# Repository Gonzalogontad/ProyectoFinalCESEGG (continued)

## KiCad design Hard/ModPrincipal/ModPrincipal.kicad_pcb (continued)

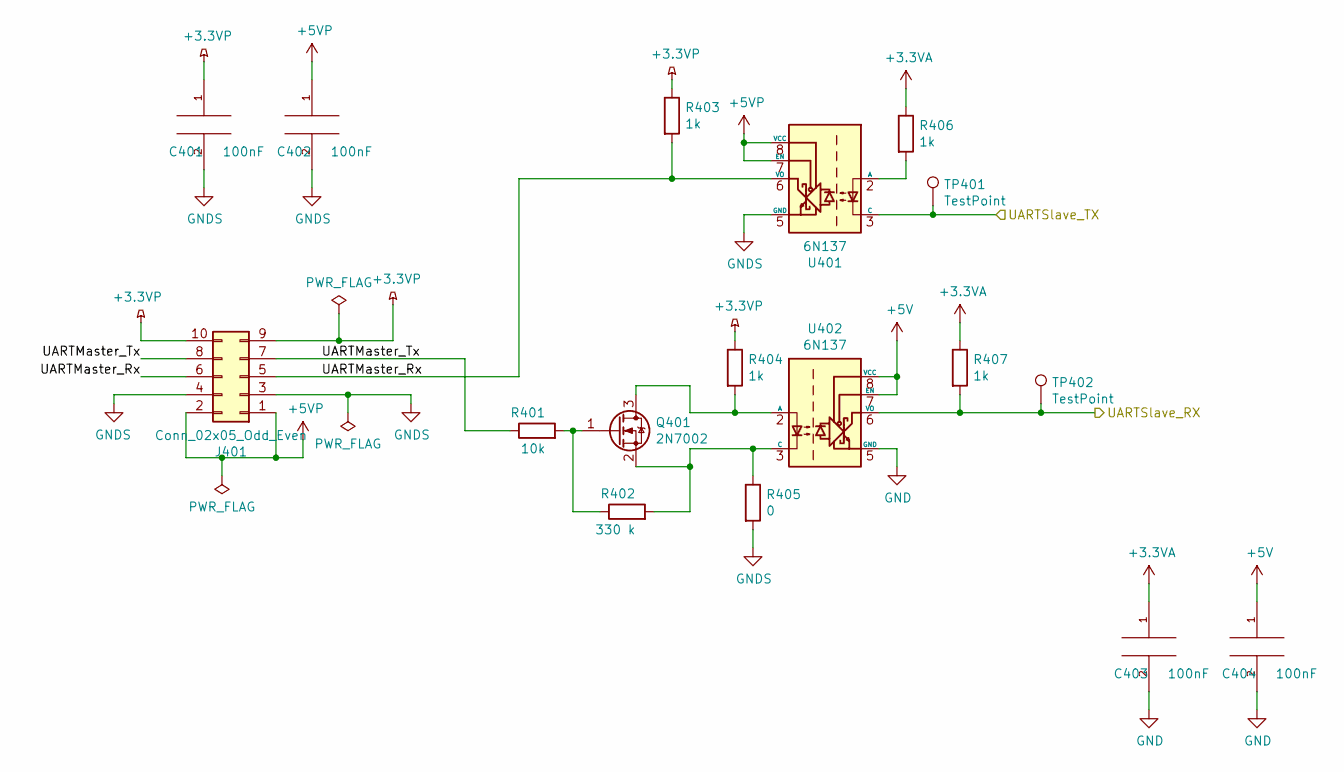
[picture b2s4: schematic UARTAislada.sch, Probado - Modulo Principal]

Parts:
C401, C402, C403, C404: 100nF; C_0805_2012Metric_Pad1.15x1.40mm_HandSolder
J401: Conn_02x05_Odd_Even; PinHeader_2x05_P2.54mm_Vertical
Q401: 2N7002; SOT-23
R401: 10k; R_0805_2012Metric_Pad1.15x1.40mm_HandSolder
R402: 330 k; R_0805_2012Metric_Pad1.15x1.40mm_HandSolder
R403, R404, R406, R407: 1k; R_0805_2012Metric_Pad1.15x1.40mm_HandSolder
R405: 0; R_0805_2012Metric_Pad1.15x1.40mm_HandSolder
TP401, TP402: TestPoint; TestPoint_Pad_D1.5mm
U401, U402: 6N137; DIP-8_W7.62mm

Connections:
+3.3VA: C403.1, R406.1, R407.1; also elsewhere on the board
+3.3VP: C401.1, J401.9, J401.10, R403.1, R404.1
+5V: C404.1, U402.7 (EN), U402.8 (VCC); also elsewhere on the board
+5VP: C402.1, J401.1, J401.2, U401.7 (EN), U401.8 (VCC)
/UARTAislada/UARTMaster_Rx: J401.5, J401.6, R403.2, U401.6 (VO)
/UARTAislada/UARTMaster_Tx: J401.7, J401.8, R401.1
/UARTAislada/UARTSlave_RX: R407.2, TP402.1, U402.6 (VO); also elsewhere on the board
/UARTAislada/UARTSlave_TX: TP401.1, U401.3 (C); also elsewhere on the board
GND: C403.2, C404.2, U402.5 (GND); also elsewhere on the board
GNDS: C401.2, C402.2, J401.3, J401.4, R405.2, U401.5 (GND)
unnamed: Q401.1 (G), R401.2, R402.1
unnamed: Q401.2 (S), R402.2, R405.1, U402.3 (C)
unnamed: Q401.3 (D), R404.2, U402.2 (A)
unnamed: R406.2, U401.2 (A)

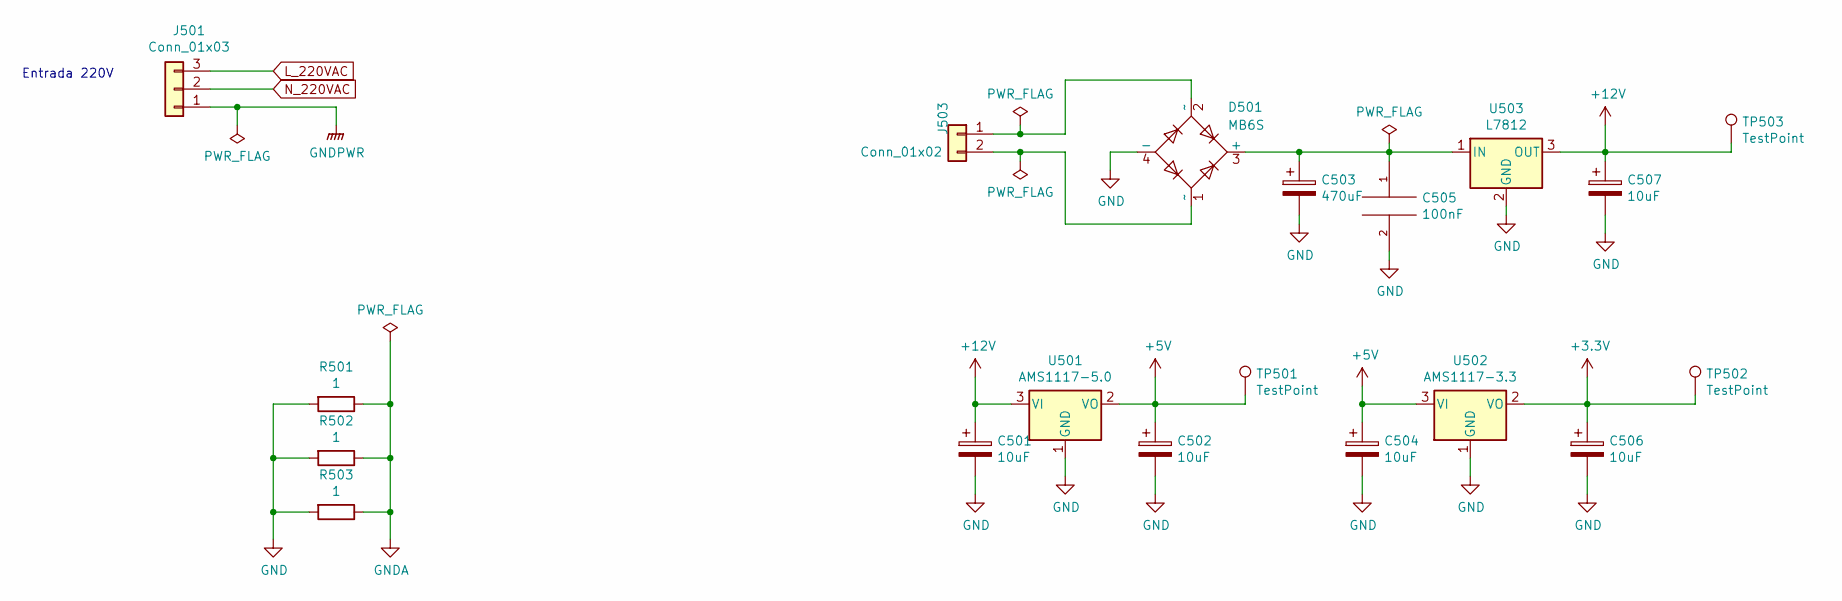
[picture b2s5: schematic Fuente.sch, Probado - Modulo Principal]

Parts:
C501, C502, C504, C506, C507: 10uF; C_1206_3216Metric_Pad1.42x1.75mm_HandSolder
C503: 470uF; CP_Radial_D8.0mm_P3.50mm
C505: 100nF; C_0805_2012Metric_Pad1.15x1.40mm_HandSolder
D501: MB6S; SO-4_4.4x4.3mm_P2.54mm
J501: Conn_01x03; TerminalBlock_bornier-3_P5.00mm
J503: Conn_01x02; TerminalBlock_bornier-2_P5.00mm
R501, R502, R503: 1; R_0805_2012Metric_Pad1.15x1.40mm_HandSolder
TP501, TP502, TP503: TestPoint; TestPoint_Pad_D1.5mm
U501: AMS1117-5.0; SOT-223-3_TabPin2
U502: AMS1117-3.3; SOT-223-3_TabPin2
U503: L7812; TO-220-3_Vertical

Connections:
+3V3: C506.1, TP502.1, U502.2 (VO); also elsewhere on the board
+5V: C502.1, C504.1, TP501.1, U501.2 (VO), U502.3 (VI); also elsewhere on the board
+12V: C501.1, C507.1, TP503.1, U501.3 (VI), U503.3 (OUT); also elsewhere on the board
GND: C501.2, C502.2, C503.2, C504.2, C505.2, C506.2, C507.2, D501.4 (-), R501.2, R502.2, R503.2, U501.1 (GND), U502.1 (GND), U503.2 (GND); also elsewhere on the board
GNDA: R501.1, R502.1, R503.1; also elsewhere on the board
GNDPWR: J501.1; also elsewhere on the board
L_220VAC: J501.3; also elsewhere on the board
N_220VAC: J501.2; also elsewhere on the board
unnamed: C503.1, C505.1, D501.3 (+), U503.1 (IN)
unnamed: D501.1 (~~), J503.2
unnamed: D501.2 (~~), J503.1

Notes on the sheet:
Entrada 220V

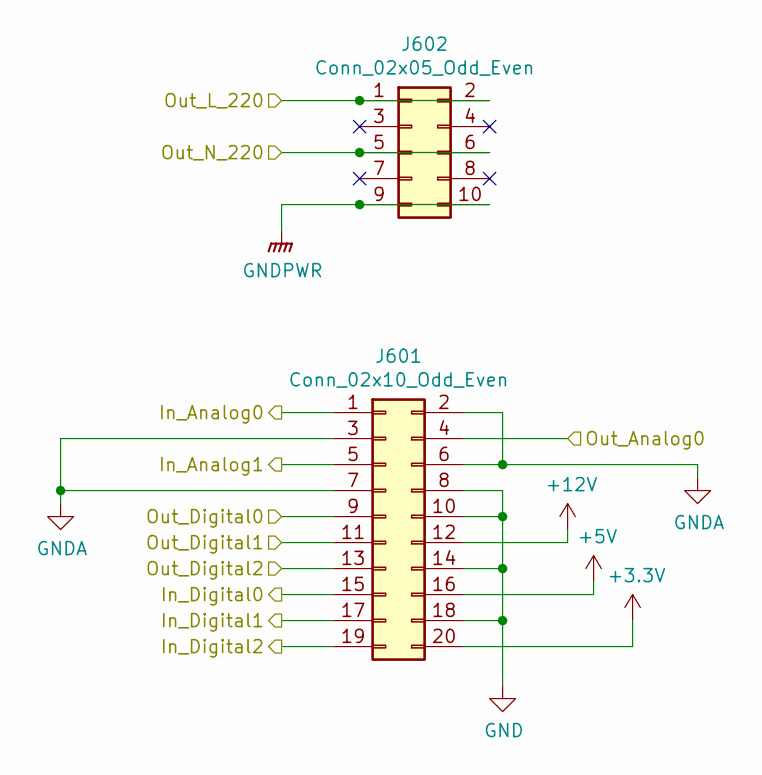
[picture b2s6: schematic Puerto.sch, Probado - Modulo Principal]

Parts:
J601: Conn_02x10_Odd_Even; PinSocket_2x10_P2.54mm_Horizontal
J602: Conn_02x05_Odd_Even; PinSocket_2x03_Doble_Paso_P2.54mm_Horizontal

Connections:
+3V3: J601.20; also elsewhere on the board
+5V: J601.16; also elsewhere on the board
+12V: J601.12; also elsewhere on the board
/AnalogInputs/Analog0: J601.1; also elsewhere on the board
/AnalogInputs/Analog1: J601.5; also elsewhere on the board
/AnalogOut/AnalogOut: J601.4; also elsewhere on the board
/IOs digitales/Entrada0: J601.15; also elsewhere on the board
/IOs digitales/Entrada1: J601.17; also elsewhere on the board
/IOs digitales/Entrada2: J601.19; also elsewhere on the board
/IOs digitales/L_220V_Out: J602.1, J602.2; also elsewhere on the board
/IOs digitales/N_220V_Out: J602.5, J602.6; also elsewhere on the board
/Puerto/Out_Digital0: J601.9; also elsewhere on the board
/Puerto/Out_Digital1: J601.11; also elsewhere on the board
/Puerto/Out_Digital2: J601.13; also elsewhere on the board
GND: J601.8, J601.10, J601.14, J601.18; also elsewhere on the board
GNDA: J601.2, J601.3, J601.6, J601.7; also elsewhere on the board
GNDPWR: J602.9, J602.10; also elsewhere on the board

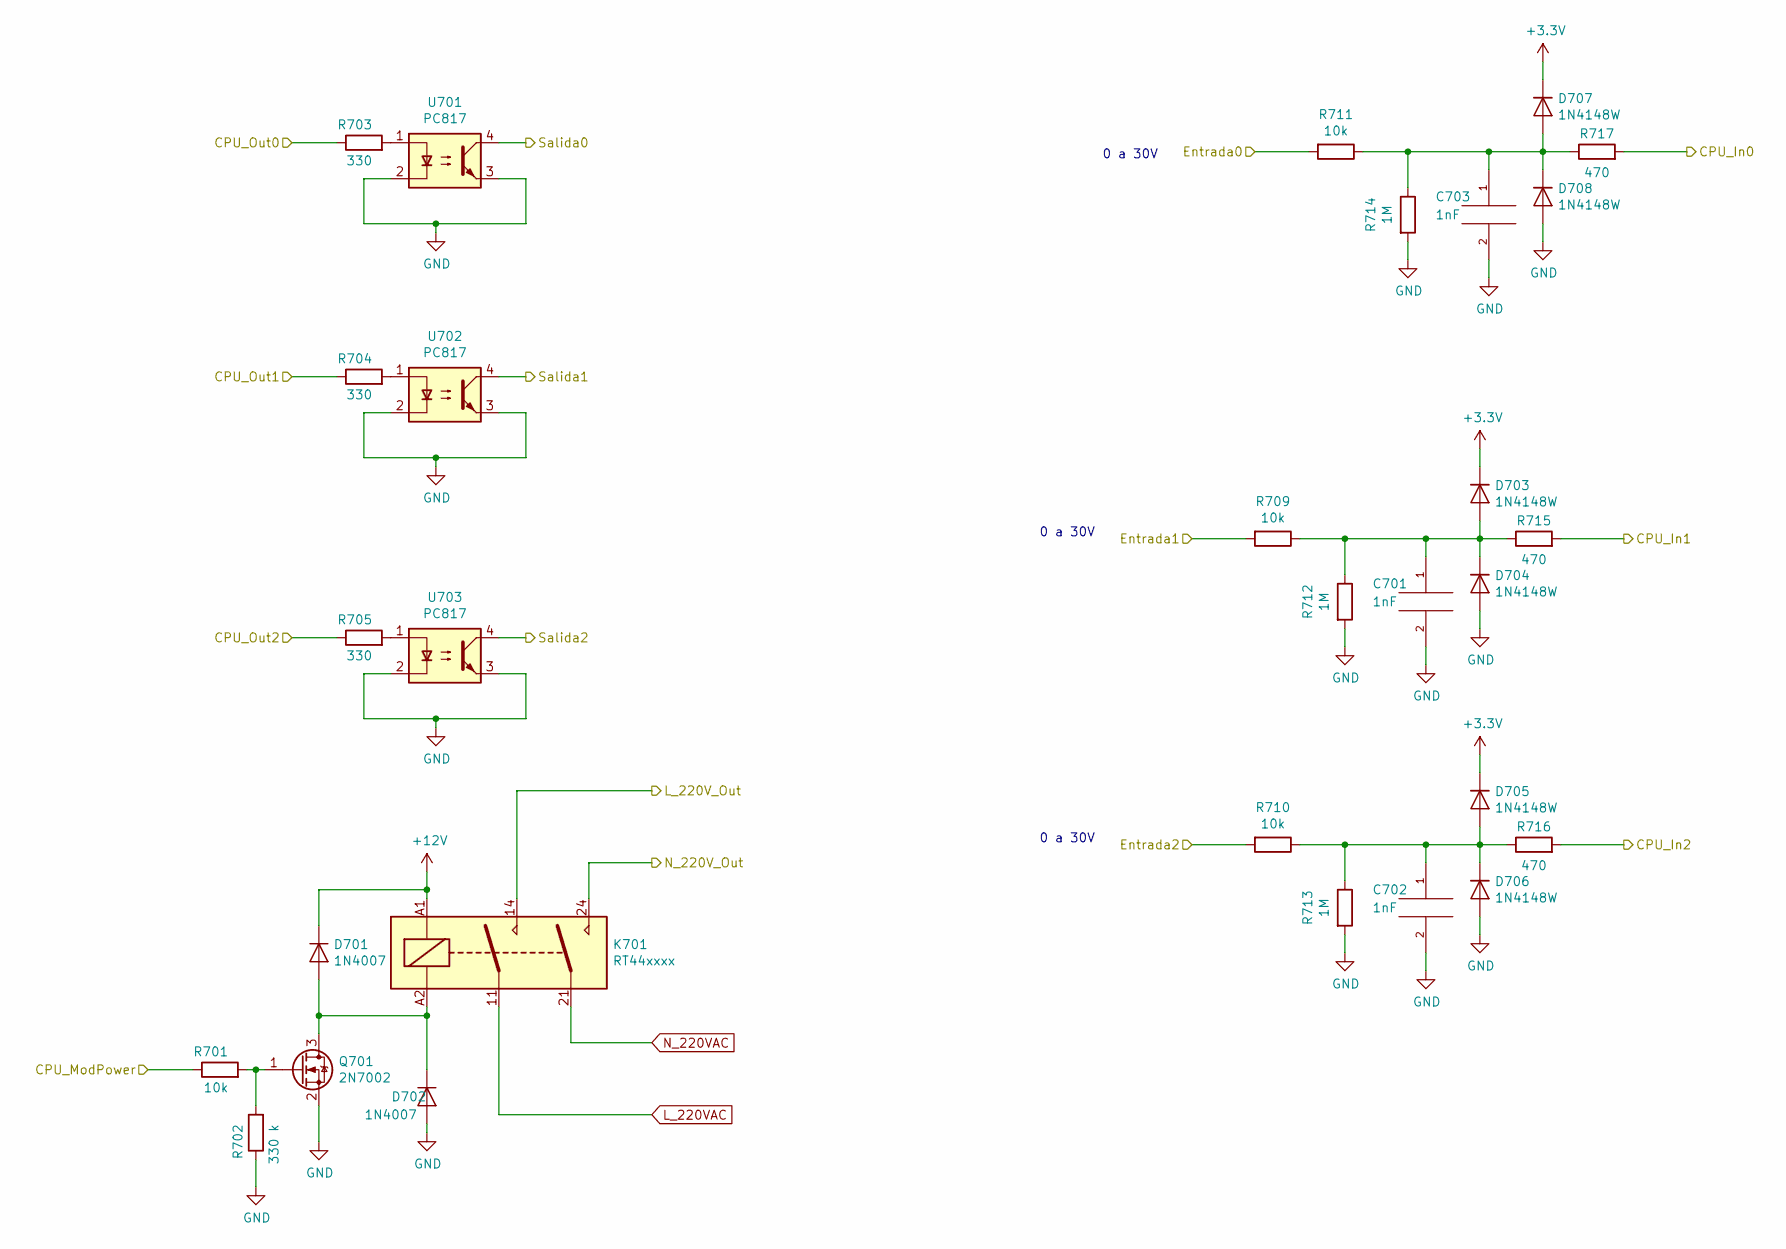
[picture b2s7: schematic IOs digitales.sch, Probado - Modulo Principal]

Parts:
C701, C702, C703: 1nF; C_0805_2012Metric_Pad1.15x1.40mm_HandSolder
D701, D702: 1N4007; D_DO-41_SOD81_P10.16mm_Horizontal
D703, D704, D705, D706, D707, D708: 1N4148W; D_MiniMELF
K701: RT44xxxx; Relay_DPST_Schrack-RT2-FormA_RM5mm
Q701: 2N7002; SOT-23
R701, R709, R710, R711: 10k; R_0805_2012Metric_Pad1.15x1.40mm_HandSolder
R702: 330 k; R_0805_2012Metric_Pad1.15x1.40mm_HandSolder
R703, R704, R705: 330; R_0805_2012Metric_Pad1.15x1.40mm_HandSolder
R712, R713, R714: 1M; R_0805_2012Metric_Pad1.15x1.40mm_HandSolder
R715, R716, R717: 470; R_0805_2012Metric_Pad1.15x1.40mm_HandSolder
U701, U702, U703: PC817; SO-4_7.6x3.6mm_P2.54mm

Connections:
+3V3: D703.1 (K), D705.1 (K), D707.1 (K); also elsewhere on the board
+12V: D701.1 (K), K701.A1; also elsewhere on the board
/IOs digitales/CPU_In0: R717.2; also elsewhere on the board
/IOs digitales/CPU_In1: R715.2; also elsewhere on the board
/IOs digitales/CPU_In2: R716.2; also elsewhere on the board
/IOs digitales/CPU_ModPower: R701.1; also elsewhere on the board
/IOs digitales/CPU_Out0: R703.1; also elsewhere on the board
/IOs digitales/CPU_Out1: R704.1; also elsewhere on the board
/IOs digitales/CPU_Out2: R705.1; also elsewhere on the board
/IOs digitales/Entrada0: R711.2; also elsewhere on the board
/IOs digitales/Entrada1: R709.2; also elsewhere on the board
/IOs digitales/Entrada2: R710.2; also elsewhere on the board
/IOs digitales/L_220V_Out: K701.14; also elsewhere on the board
/IOs digitales/N_220V_Out: K701.24; also elsewhere on the board
/Puerto/Out_Digital0: U701.4; also elsewhere on the board
/Puerto/Out_Digital1: U702.4; also elsewhere on the board
/Puerto/Out_Digital2: U703.4; also elsewhere on the board
GND: C701.2, C702.2, C703.2, D702.2 (A), D704.2 (A), D706.2 (A), D708.2 (A), Q701.2 (S), R702.1, R712.2, R713.2, R714.2, U701.2, U701.3, U702.2, U702.3, U703.2, U703.3; also elsewhere on the board
L_220VAC: K701.11; also elsewhere on the board
N_220VAC: K701.21; also elsewhere on the board
unnamed: C701.1, D703.2 (A), D704.1 (K), R709.1, R712.1, R715.1
unnamed: C702.1, D705.2 (A), D706.1 (K), R710.1, R713.1, R716.1
unnamed: C703.1, D707.2 (A), D708.1 (K), R711.1, R714.1, R717.1
unnamed: D701.2 (A), D702.1 (K), K701.A2, Q701.3 (D)
unnamed: Q701.1 (G), R701.2, R702.2
unnamed: R703.2, U701.1
unnamed: R704.2, U702.1
unnamed: R705.2, U703.1

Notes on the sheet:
0 a 30V

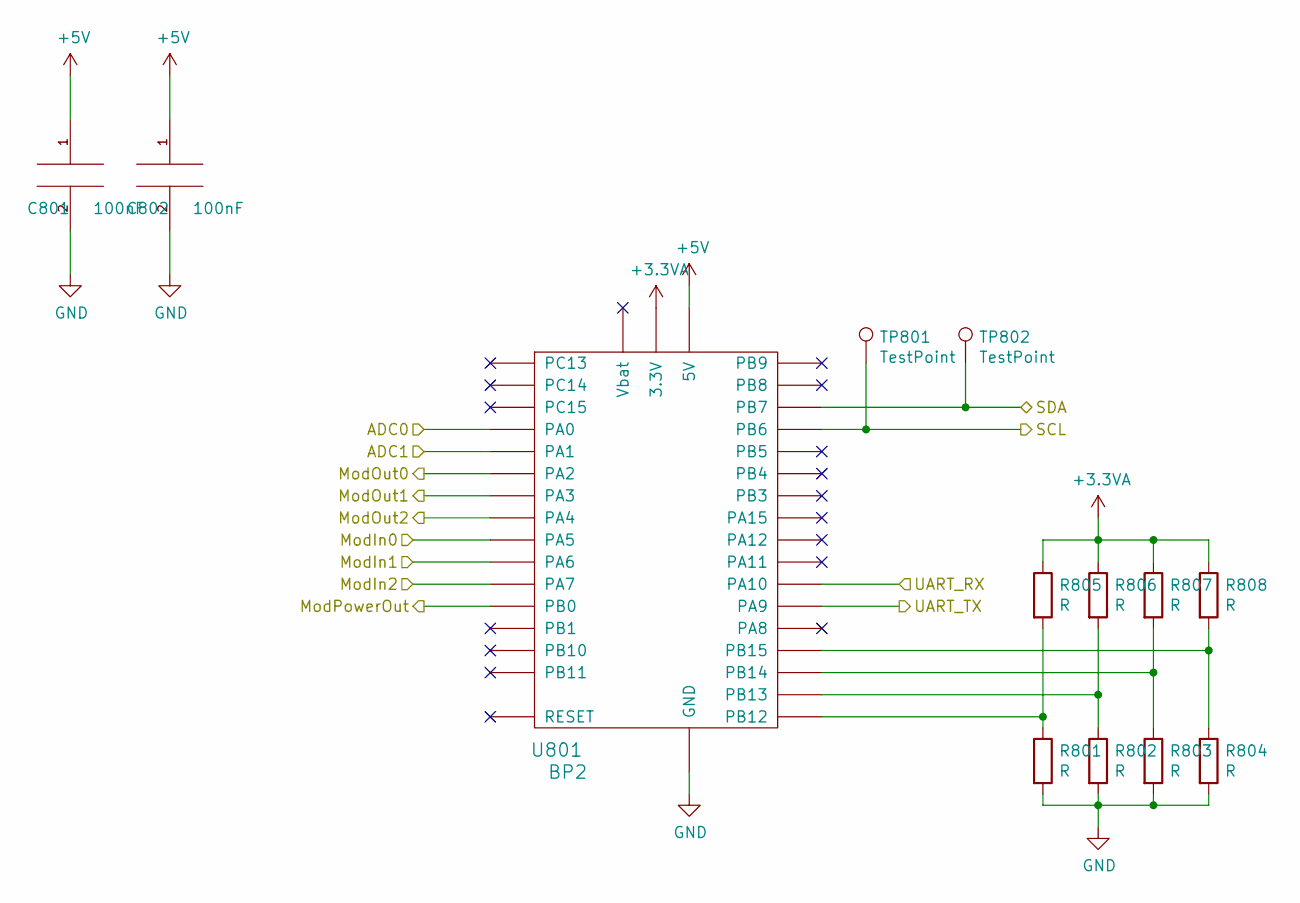
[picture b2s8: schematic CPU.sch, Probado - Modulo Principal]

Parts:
C801, C802: 100nF; C_0805_2012Metric_Pad1.15x1.40mm_HandSolder
R801, R802, R803, R804, R805, R806, R807, R808: R; R_0805_2012Metric_Pad1.15x1.40mm_HandSolder
TP801, TP802: TestPoint; TestPoint_Pad_D1.5mm
U801: BP2; BLUEPILL2

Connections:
+3.3VA: R805.1, R806.1, R807.1, R808.1, U801.3V3 (3.3V); also elsewhere on the board
+5V: C801.1, C802.1, U801.5V; also elsewhere on the board
/AnalogInputs/ADC0: U801.PA0; also elsewhere on the board
/AnalogInputs/ADC1: U801.PA1; also elsewhere on the board
/AnalogOut/SCL: TP801.1, U801.PB6; also elsewhere on the board
/AnalogOut/SDA: TP802.1, U801.PB7; also elsewhere on the board
/IOs digitales/CPU_In0: U801.PA5; also elsewhere on the board
/IOs digitales/CPU_In1: U801.PA6; also elsewhere on the board
/IOs digitales/CPU_In2: U801.PA7; also elsewhere on the board
/IOs digitales/CPU_ModPower: U801.PB0; also elsewhere on the board
/IOs digitales/CPU_Out0: U801.PA2; also elsewhere on the board
/IOs digitales/CPU_Out1: U801.PA3; also elsewhere on the board
/IOs digitales/CPU_Out2: U801.PA4; also elsewhere on the board
/UARTAislada/UARTSlave_RX: U801.PA10; also elsewhere on the board
/UARTAislada/UARTSlave_TX: U801.PA9; also elsewhere on the board
GND: C801.2, C802.2, R801.2, R802.2, R803.2, R804.2, U801.G (GND); also elsewhere on the board
unnamed: R801.1, R805.2, U801.PB12
unnamed: R802.1, R806.2, U801.PB13
unnamed: R803.1, R807.2, U801.PB14
unnamed: R804.1, R808.2, U801.PB15

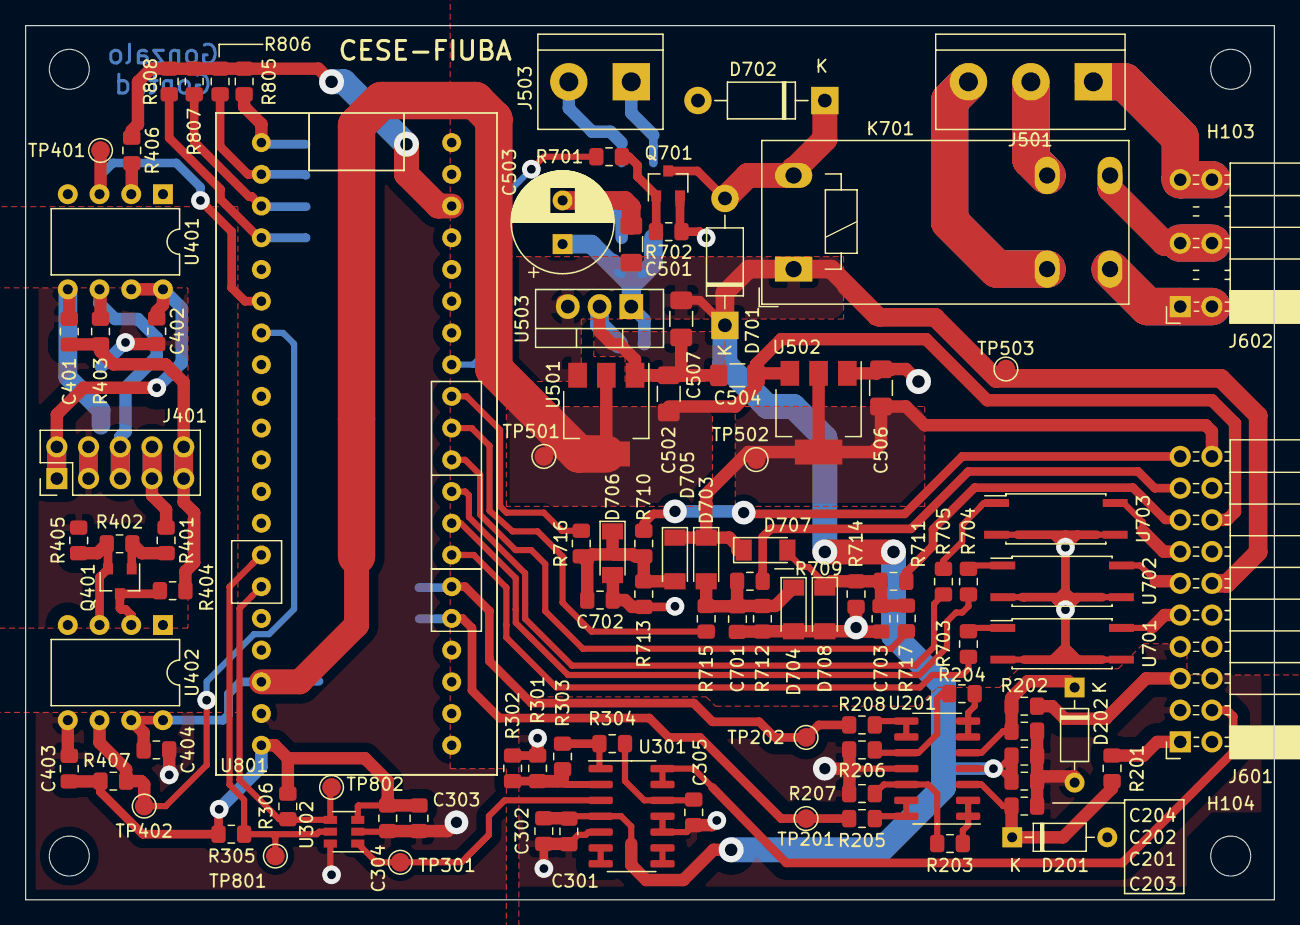
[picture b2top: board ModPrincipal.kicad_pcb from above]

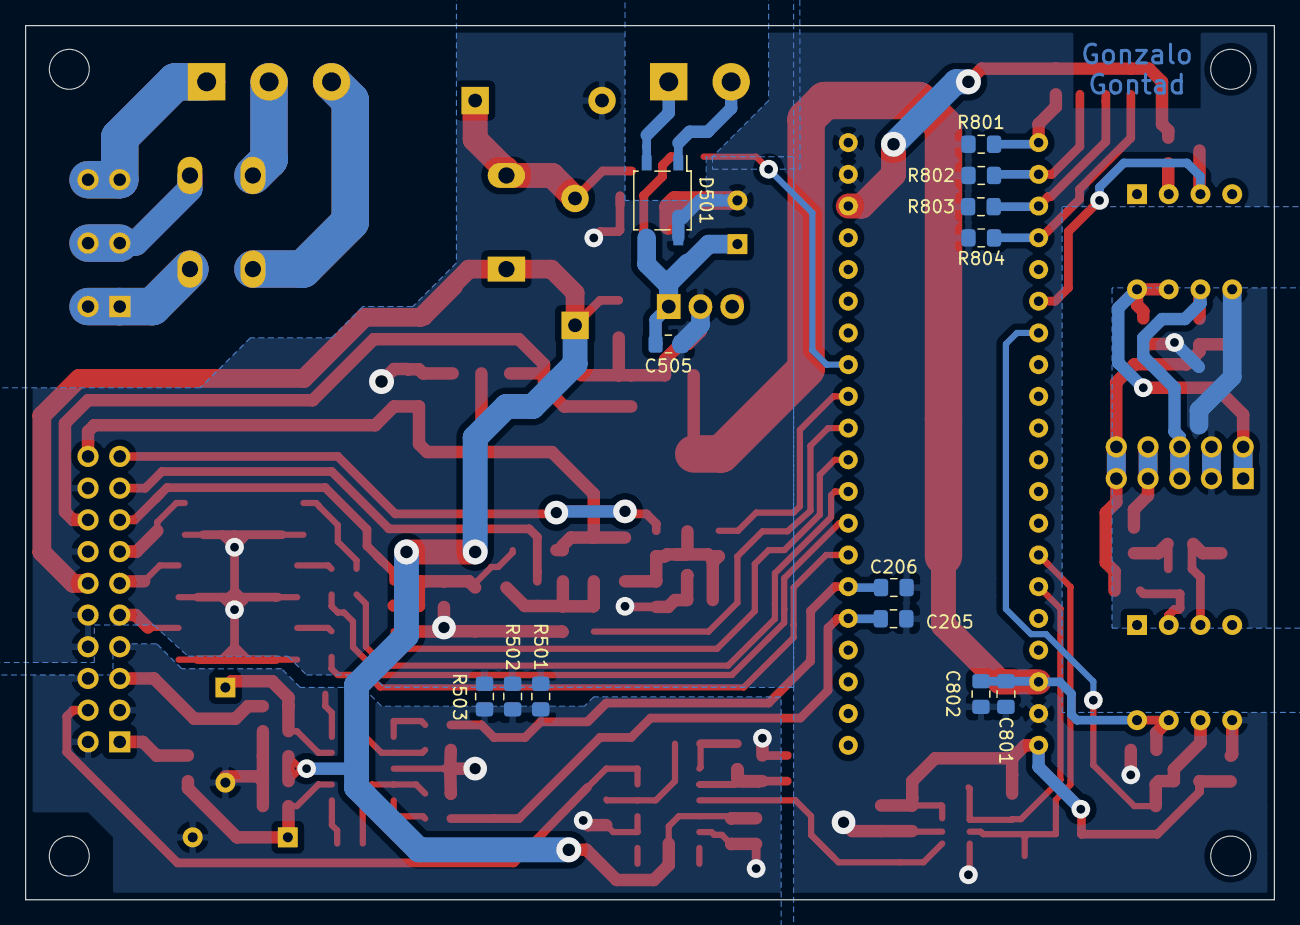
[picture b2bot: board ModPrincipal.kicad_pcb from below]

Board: 2 copper layers, 100.0 x 70.0 mm, 118 parts (13 on the bottom side), 71 nets.

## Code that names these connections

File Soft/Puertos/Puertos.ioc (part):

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Mcu.Name=STM32F103C(8-B)Tx
Mcu.Package=LQFP48
Mcu.UserName=STM32F103C8Tx
PA0-WKUP.Signal=ADCx_IN0
PA1.Signal=ADCx_IN1
PA10.Mode=Asynchronous
PA10.Signal=USART1_RX
PA13.Mode=Serial_Wire
PA13.Signal=SYS_JTMS-SWDIO
PA14.Mode=Serial_Wire
PA14.Signal=SYS_JTCK-SWCLK
PA2.GPIOParameters=GPIO_Label
PA2.GPIO_Label=ModuleOut0
PA2.Signal=GPIO_Output
PA3.GPIOParameters=GPIO_Label
PA3.GPIO_Label=ModuleOut1
PA3.Signal=GPIO_Output
PA4.GPIOParameters=GPIO_Label
PA4.GPIO_Label=ModuleOut2
PA4.Signal=GPIO_Output
PA5.GPIOParameters=GPIO_Label
PA5.GPIO_Label=ModuleIn0
PA5.Signal=GPIO_Input
PA6.GPIOParameters=GPIO_Label
PA6.GPIO_Label=ModuleIn1
PA6.Signal=GPIO_Input
PA7.GPIOParameters=GPIO_Label
PA7.GPIO_Label=ModuleIn2
PA7.Signal=GPIO_Input
PA9.Mode=Asynchronous
PA9.Signal=USART1_TX
PB0.Signal=GPIO_Output
PB12.GPIOParameters=GPIO_Label
PB12.GPIO_Label=ModuelAddr0
PB12.Signal=GPIO_Input
PB13.GPIOParameters=GPIO_Label
PB13.GPIO_Label=ModuelAddr1
PB13.Signal=GPIO_Input
PB14.GPIOParameters=GPIO_Label
PB14.GPIO_Label=ModuelAddr2
PB14.Signal=GPIO_Input
PB15.GPIOParameters=GPIO_Label
PB15.GPIO_Label=ModuelAddr3
PB15.Signal=GPIO_Input
PB3.Signal=GPIO_Input
PB4.Signal=GPIO_Input
PB5.Signal=GPIO_Input
PB6.GPIOParameters=GPIO_Label
PB6.GPIO_Label=DAC_SCL
PB6.Mode=I2C
PB6.Signal=I2C1_SCL
PB7.GPIOParameters=GPIO_Label
PB7.GPIO_Label=DAC_SDA
PB7.Mode=I2C
PB7.Signal=I2C1_SDA
PC13-TAMPER-RTC.GPIOParameters=GPIO_Label
PC13-TAMPER-RTC.GPIO_Label=ModuleHeartBeat
PC13-TAMPER-RTC.Signal=GPIO_Output
RCC.SYSCLKFreq_VALUE=64000000
RCC.SYSCLKSource=RCC_SYSCLKSOURCE_PLLCLK
board=custom

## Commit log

2020-05-21 Creo proyecto de Hardware del modulo principal
2020-05-21 Creo proyecto de Hardware modulo principal
2020-05-22 Agrego Etapa de entrada ADCs
2020-05-26 Agrego etapa de salida del DAC
2020-05-27 Agrego UART aislada y salidas digitales
2020-05-28 Agrego fuente de alimentación
2020-05-28 Asignacion inicial de footprints
2020-05-29 Asignación de footprint y corrección de errores de ERC en esquematico
2020-05-29 Inicio ubicacion de componentes
2020-05-30 Avance en place de componentes
2020-05-31 Avance en trazado de pista Modulo principal
2020-06-01 Trazado completo de PCB modulo principal V1.0
2020-06-01 Inicio Modulos Adicionales
2020-06-02 Completado de esquematico en modulos adicionales
2020-06-02 Primera correccion en modulos Adicionales y cambio de etapa de salida en modulo principal
2020-06-02 Asignacion de footprints Modulos adicionales
2020-06-03 Inicio placement de componentes en Modulos Adicionales
2020-06-03 Avance en trazado de PCB modulos Adicionales
2020-06-04 Avance en trazado de pistas Modulos Adicionales
2020-06-04 Primera version de PCBs para fabricar
2020-06-04 Gerbers para fabricacion
2020-06-16 Etapa de transmision del driver de Puertos
2020-06-18 Agrego driver de UART de ESP
2020-07-04 Avance en servidor
2020-07-10 Avance en tarea interpreter
2020-07-16 Correccion de bug en interpreter
2020-07-16 Agrego comentarios
2020-10-05 Codigo a comentar
2020-10-28 Completo comentarios y agrego el firmware para el STM32.
